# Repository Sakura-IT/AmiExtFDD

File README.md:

Interface to connect floppy drives to Amiga, externally.

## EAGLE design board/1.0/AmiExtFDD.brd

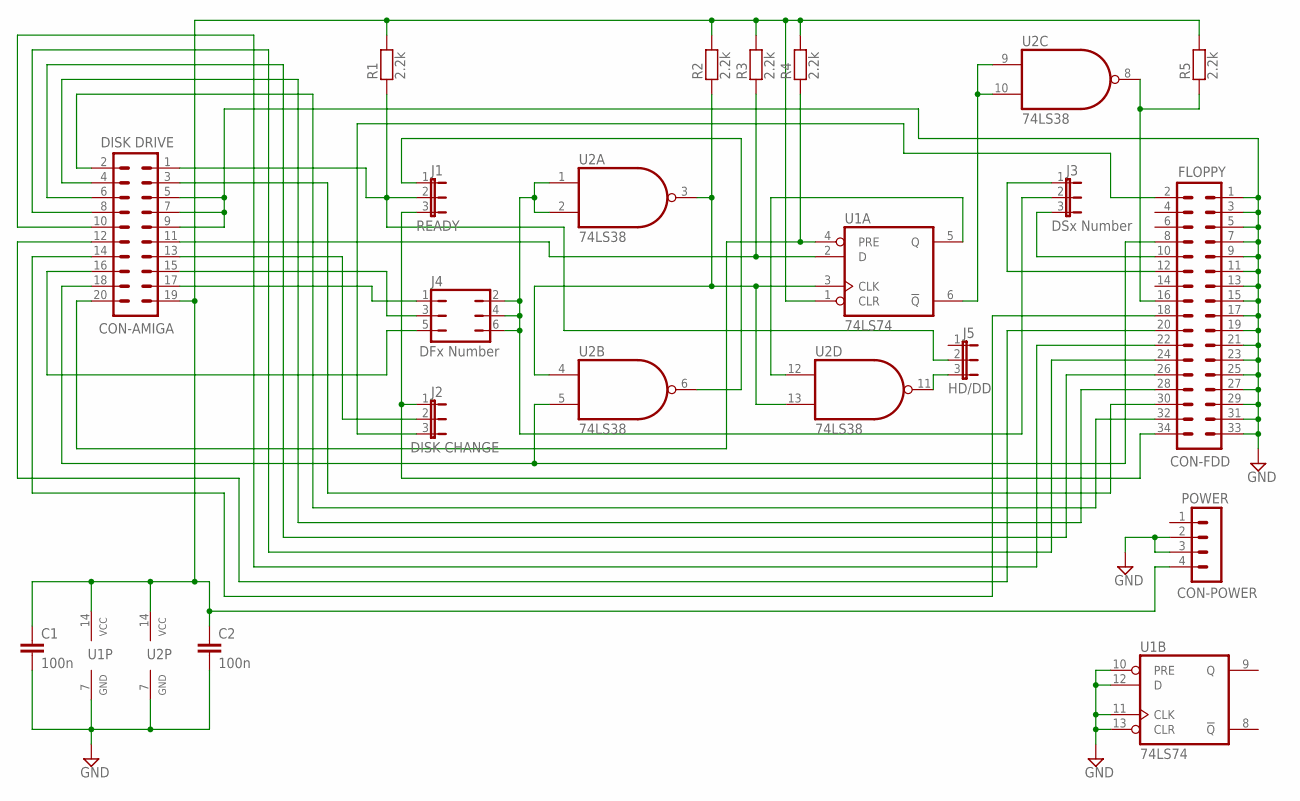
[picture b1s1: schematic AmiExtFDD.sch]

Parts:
C1, C2: 100n; SMD-UNI
CON-AMIGA: DISK DRIVE; IDC20
CON-FDD: FLOPPY; FDD2
CON-POWER: POWER; MINI-MOLEX
J1: READY; JP3X1-UNI
J2: DISK CHANGE; JP3X1-UNI
J3: DSx Number; JP3X1-UNI
J4: DFx Number; JP3X2-UNI
J5: HD/DD; JP3X1-UNI
R1, R2, R3, R4, R5: 2.2k; SMD-UNI
U1: 74LS74; SO14
U2: 74LS38; SO14

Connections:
1: CON-POWER.1
GND: C1.2, C2.2, CON-AMIGA.5, CON-AMIGA.7, CON-AMIGA.9, CON-FDD.1, CON-FDD.3, CON-FDD.5, CON-FDD.7, CON-FDD.9, CON-FDD.11, CON-FDD.13, CON-FDD.15, CON-FDD.17, CON-FDD.19, CON-FDD.21, CON-FDD.23, CON-FDD.25, CON-FDD.27, CON-FDD.29, CON-FDD.31, CON-FDD.33, CON-POWER.2, CON-POWER.3, U1.7 (GND), U1.10 (PRE), U1.11 (CLK), U1.12 (D), U1.13 (CLR), U2.7 (GND)
unnamed: CON-AMIGA.13, J2.2
unnamed: U1.5 (Q), U2.12 (I0)
unnamed: CON-FDD.16, R5.1, U2.8 (O)
unnamed: U1.6 (!Q), U2.9 (I0), U2.10 (I1)
unnamed: R2.1, U1.3 (CLK), U2.3 (O), U2.4 (I0), U2.13 (I1)
unnamed: J5.3, U2.11 (O)
unnamed: CON-AMIGA.17, J4.1
unnamed: CON-FDD.34, J1.3, J2.1
unnamed: CON-FDD.2, J2.3
unnamed: J1.1, U2.6 (O)
unnamed: CON-AMIGA.1, J1.2, J5.2, R1.1
unnamed: CON-AMIGA.15, J4.3
unnamed: CON-FDD.12, J3.1
unnamed: CON-AMIGA.16, J4.5
unnamed: J3.2, J4.2, J4.4, J4.6, U2.1 (I0), U2.2 (I1)
unnamed: CON-AMIGA.18, CON-FDD.8, U2.5 (I1)
unnamed: CON-FDD.10, J3.3
unnamed: CON-AMIGA.3, CON-FDD.30
unnamed: CON-AMIGA.11, R3.1, U1.2 (D)
unnamed: C1.1, C2.1, CON-AMIGA.19, CON-POWER.4, R1.2, R2.2, R3.2, R4.2, R5.2, U1.1 (CLR), U1.14 (VCC), U2.14 (VCC)
unnamed: CON-AMIGA.4, CON-FDD.28
unnamed: CON-AMIGA.6, CON-FDD.26
unnamed: CON-AMIGA.2, CON-FDD.32
unnamed: CON-AMIGA.8, CON-FDD.24
unnamed: CON-AMIGA.10, CON-FDD.22
unnamed: CON-AMIGA.12, CON-FDD.20
unnamed: CON-AMIGA.14, CON-FDD.18
unnamed: CON-AMIGA.20, R4.1, U1.4 (PRE)

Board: 2 copper layers, 17 parts (0 on the bottom side), 29 nets, no tracks yet.

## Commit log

2014-11-23 Initial import.
2014-11-23 Commit revision 1.0 of the board.
2014-12-06 Import misc missing files from the project.
2014-12-09 Minor fixes to power traces.
2014-12-31 Add manual (more of a template for now).
2015-01-02 Fix missing RDY connection.
2015-01-07 Gerber file of board
2015-01-30 Little change on board and scheme
2015-06-01 final version of board
